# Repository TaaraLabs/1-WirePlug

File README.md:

1-Wire Plug
==============

1-Wire to i2c bridge for TaaraNode and JeeNode

[WebSite](https://taaralabs.eu/op1)

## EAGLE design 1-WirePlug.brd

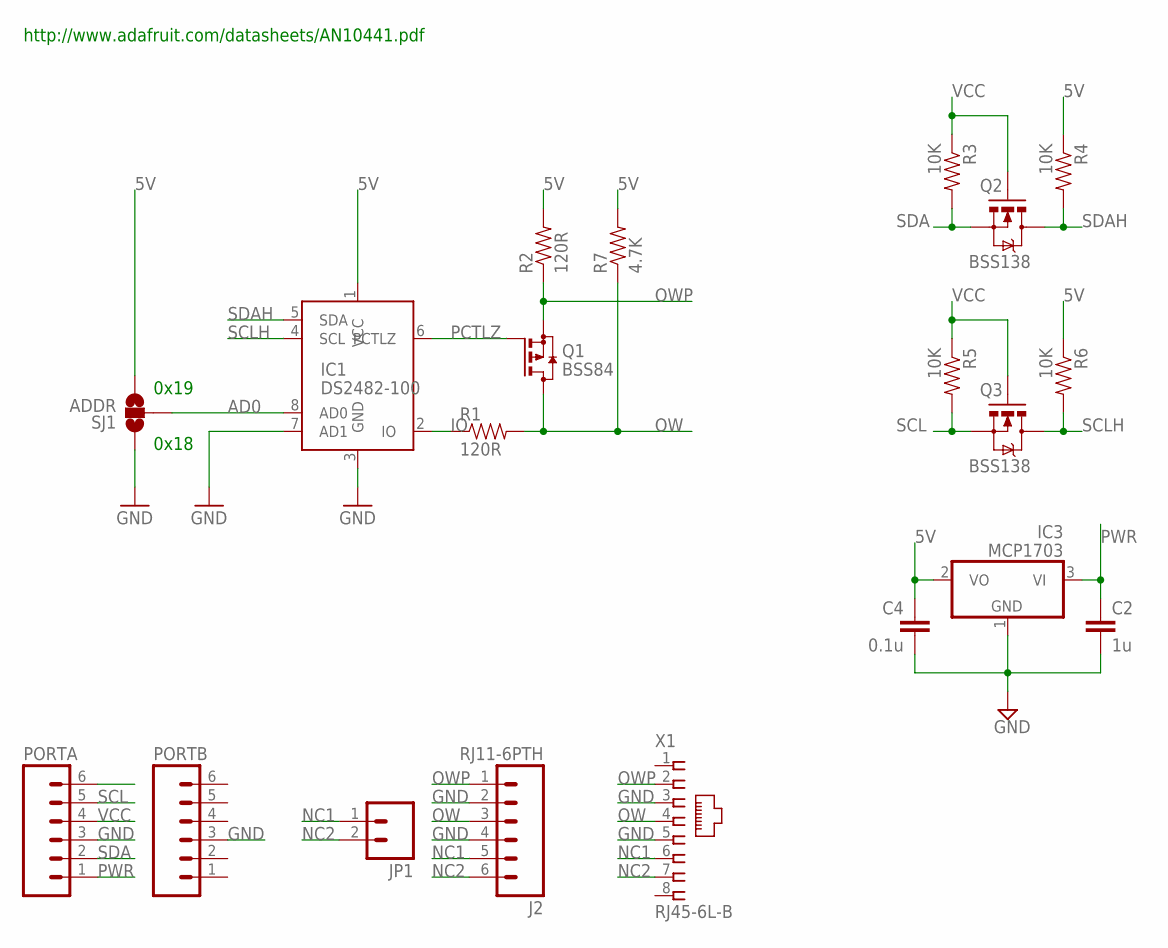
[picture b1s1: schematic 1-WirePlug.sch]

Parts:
C2: 1u; 0603-CAP
C4: 0.1u; 0603-CAP
IC1: DS2482-100; SO08
IC3: MCP1703; SOT23
J2: RJ11-6PTH; RJ11-6
JP1: M02PTH; 1X02
PORTA: M06SIP_LOCK; 1X06-SIP_LOCK
PORTB: M06SIP_LOCK; 1X06-SIP_LOCK
Q1: BSS84; SOT23
Q2, Q3: BSS138; SOT23-3
R1, R2: 120R; 0603-RES
R3, R4, R5, R6: 10K; 0603-RES
R7: 4.7K; 0603-RES
SJ1: ADDR; SJ_3_PASTE1&2
X1: RJ45-6L-B; RJ45-NO-SHIELD

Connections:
5V: C4.1, IC1.1 (VCC), IC3.2 (VO), R2.2, R4.1, R6.1, R7.2, SJ1.3
AD0: IC1.8 (AD0), SJ1.2
GND: C2.2, C4.2, IC1.3 (GND), IC1.7 (AD1), IC3.1 (GND), J2.2, J2.4, PORTA.3, PORTB.3, SJ1.1, X1.3, X1.5
IO: IC1.2 (IO), R1.1
NC1: J2.5, JP1.1, X1.6
NC2: J2.6, JP1.2, X1.7
OW: J2.3, Q1.3 (D), R1.2, R7.1, X1.4
OWP: J2.1, Q1.2 (S), R2.1, X1.2
PCTLZ: IC1.6 (PCTLZ), Q1.1 (G)
PWR: C2.1, IC3.3 (VI), PORTA.1
SCL: PORTA.5, Q3.2 (S), R5.2
SCLH: IC1.4 (SCL), Q3.3 (D), R6.2
SDA: PORTA.2, Q2.2 (S), R3.2
SDAH: IC1.5 (SDA), Q2.3 (D), R4.2
VCC: PORTA.4, Q2.1 (G), Q3.1 (G), R3.1, R5.1

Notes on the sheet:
0x18
0x19
http://www.adafruit.com/datasheets/AN10441.pdf

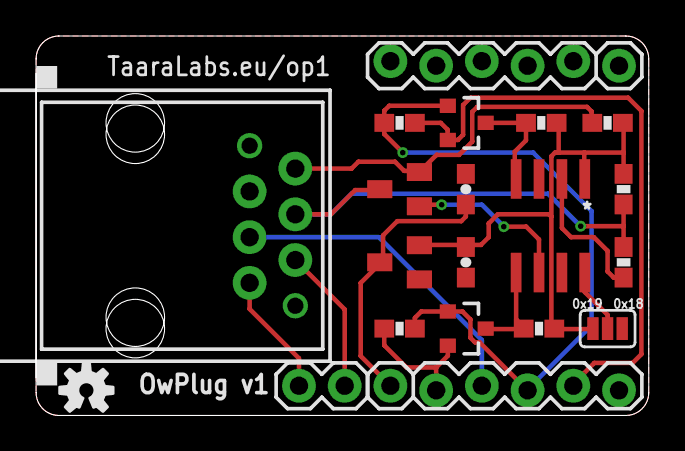
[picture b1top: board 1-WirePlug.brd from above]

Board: 2 copper layers, 34.0 x 21.1 mm, 22 parts (1 on the bottom side), 15 nets.

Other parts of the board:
U$1, U$3: OSHW-LOGO-S

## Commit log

2015-01-22 :space_invader: Added .gitattributes & .gitignore files
2015-01-22 1-Wire Plug

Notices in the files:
parts and their libraries:
SparkFun: Licensing: CC v3.0 Share-Alike You are welcome to use this library for commercial purposes.
